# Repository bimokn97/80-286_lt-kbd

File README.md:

# 286_lt Mechanical Keyboard
A mechanical keyboard from old laptop called Goldstar GPC-4013B, with STM32F401 blackpill board, and additional serial output SN74HC595.

# choose firmware
  * Diy arduino firmware
      [download](https://github.com/bimokn97/80-286_lt-kbd/blob/master/stmduino_kbd/stmduino_kbd.ino) the .ino file, and open it using arduino software, than flash it.

  * [QMK Firmware](https://github.com/qmk/qmk_firmware.git) 
    * clone the repository     : `git clone https://github.com/bimokn97/qmk_firmware.git`
    * cd to directory          : `cd qmk_firmware`
    * switch to develop branch : `git checkout develop`
    * build it                 : `make 286_lt:default` or `make 286_lt:via` for costumable layout by [via](https://caniusevia.com)
   
   * [Vial Firmware](https://github.com/vial_qmk/vial.git)
     * clone the repository     : `git clone https://github.com/bimokn97/vial_qmk.git`
     * cd to directory          : `cd qmk_firmware`
     * switch to develop branch : `git checkout develop`
     * build it                 : `make 286_lt:vial` for costumable layout by [vial]([https://caniusevia.com](https://get.vial.today/))

# pcb layout and schematic
  using [Kicad](https://www.kicad.org/)
  * [keyboard pcb](https://github.com/bimokn97/80-286_lt-kbd/tree/master/schematic_pcb/keyboard)
  * [mcu connector board](https://github.com/bimokn97/80-286_lt-kbd/tree/master/schematic_pcb/mcu_board)
  
    connector FPC 22 pin 1mm pitch
  
  *

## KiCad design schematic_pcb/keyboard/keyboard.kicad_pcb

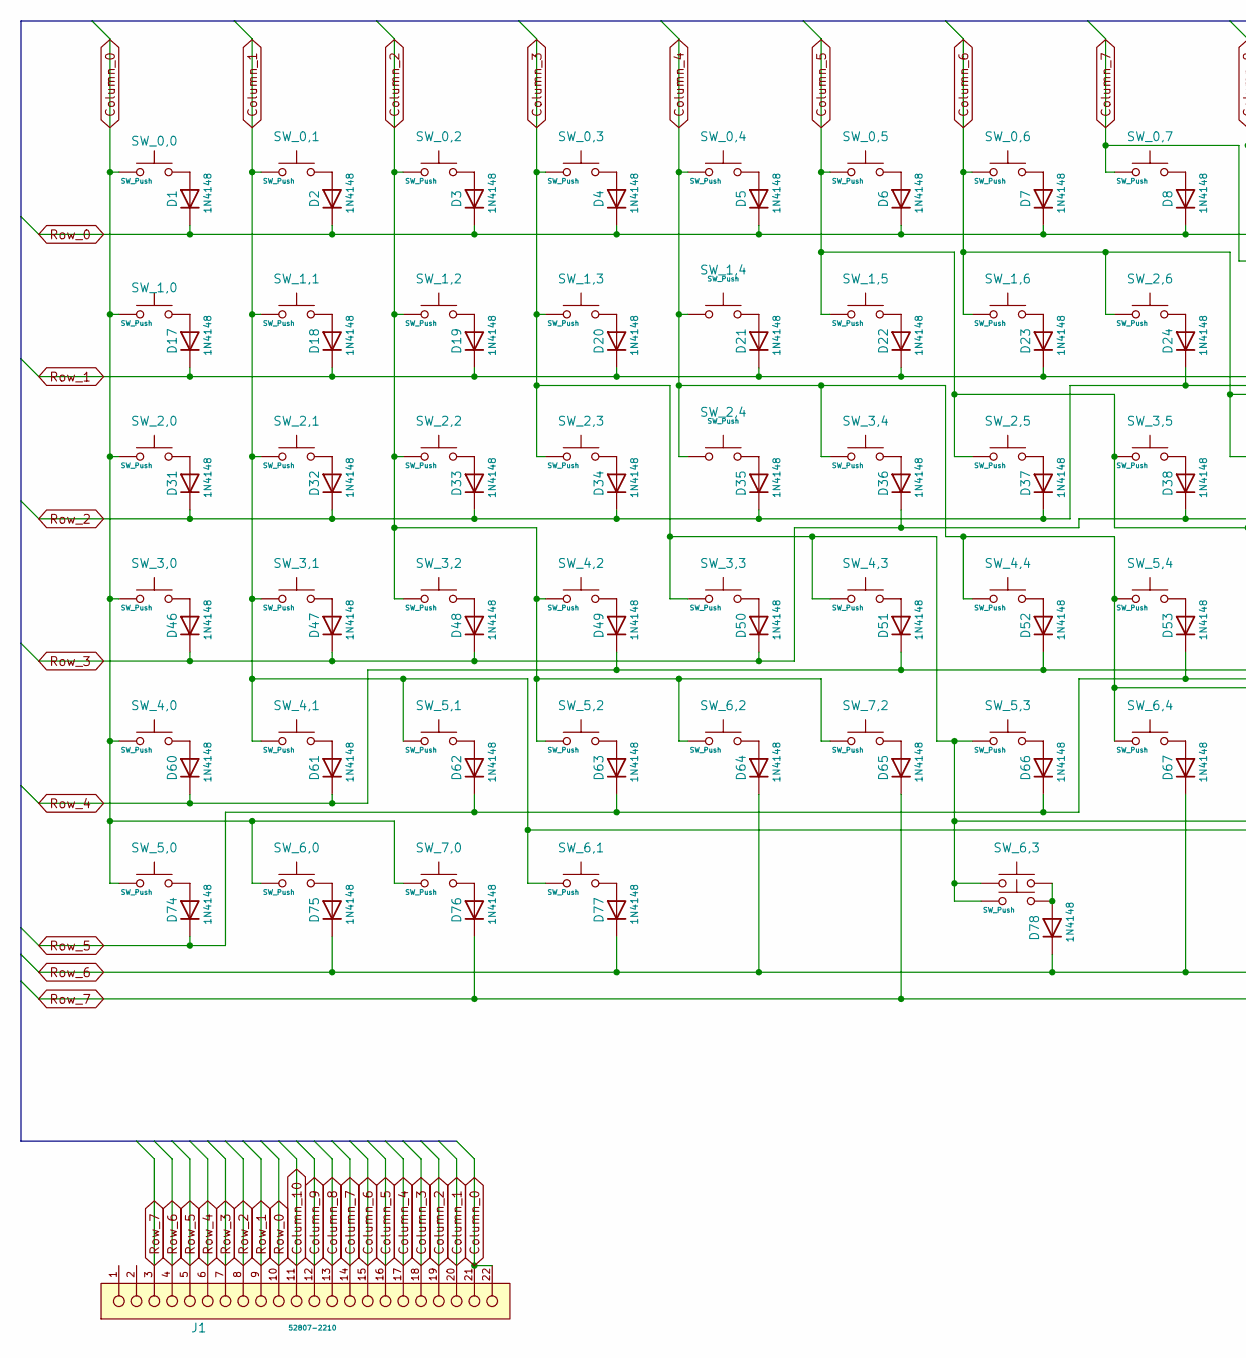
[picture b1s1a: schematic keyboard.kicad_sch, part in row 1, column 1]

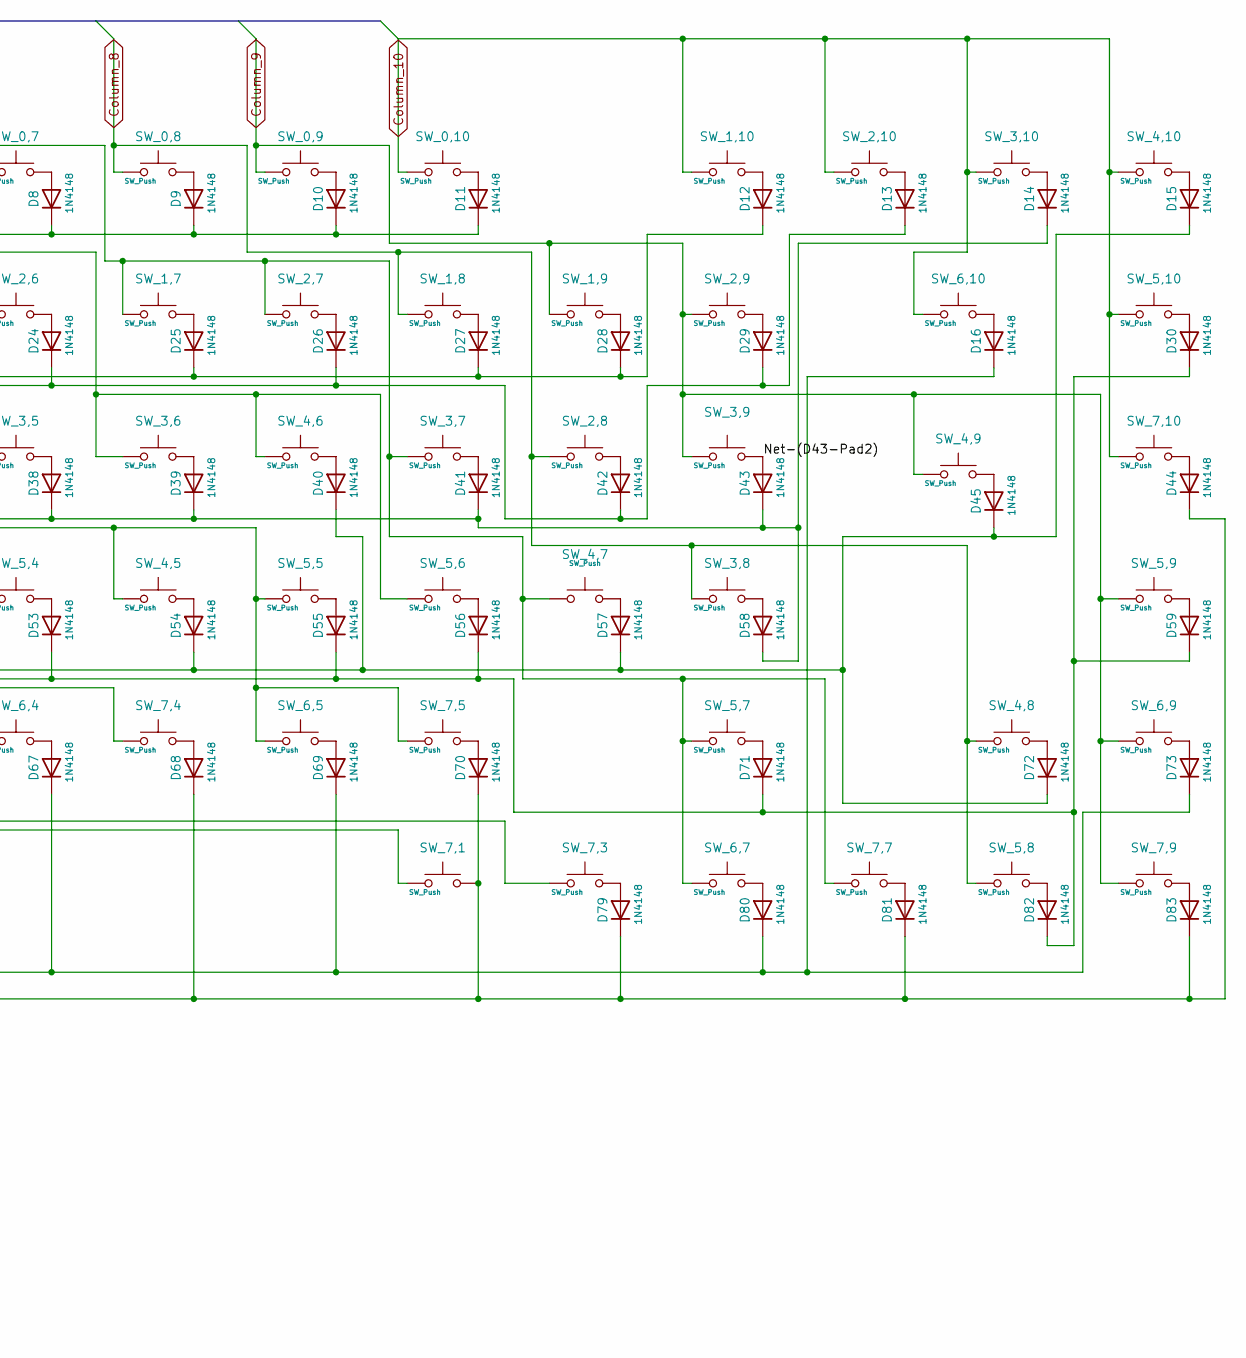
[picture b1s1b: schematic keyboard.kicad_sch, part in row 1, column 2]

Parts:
D1, D2, D3, D4, D5, D6, D7, D8, D9, D10, D11, D12, D13, D14, D15, D16, D17, D18, D19, D20, D21, D22, D23, D24, D25, D26, D27, D28, D29, D30, D31, D32, D36, D37, D38, D39, D40, D41, D42, D45, D46, D47, D48, D49, D50, D54, D55, D56, D57, D60, D61, D62, D63, D64, D65, D66, D67, D68, D69, D70, D71, D72, D76, D77, D79, D80, D81, D82: 1N4148; D_DO-35_SOD27_P12.70mm_Horizontal
D33, D34, D35, D43, D44, D51, D52, D53, D58, D59, D73, D74, D75, D83: 1N4148; D_DO-35_SOD27_P10.16mm_Horizontal
D78: 1N4148; D_DO-35_SOD27_P7.62mm_Horizontal
J1: 52807-2210; Molex-52807-2210-Manufacturer_Recommended; Voltage Max 50V
SW_0,0, SW_0,1, SW_0,2, SW_0,3, SW_0,4, SW_0,5, SW_0,6, SW_0,7, SW_0,8, SW_0,9, SW_0,10, SW_1,0, SW_1,1, SW_1,2, SW_1,3, SW_1,4, SW_1,5, SW_1,6, SW_1,7, SW_1,8, SW_1,9, SW_1,10, SW_2,1, SW_2,2, SW_2,3, SW_2,4, SW_2,5, SW_2,6, SW_2,7, SW_2,8, SW_2,9, SW_2,10, SW_3,1, SW_3,2, SW_3,3, SW_3,4, SW_3,5, SW_3,6, SW_3,7, SW_3,8, SW_3,9, SW_3,10, SW_4,1, SW_4,2, SW_4,3, SW_4,4, SW_4,5, SW_4,6, SW_4,7, SW_4,8, SW_4,10, SW_5,1, SW_5,2, SW_5,3, SW_5,4, SW_5,5, SW_5,6, SW_5,8, SW_5,9, SW_5,10, SW_6,1, SW_6,2, SW_6,4, SW_6,5, SW_6,7, SW_6,9, SW_7,0, SW_7,2, SW_7,3, SW_7,4, SW_7,5, SW_7,7, SW_7,9, SW_7,10: SW_Push; SW_Cherry_MX_Plate_1.00u
SW_2,0: SW_Push; SW_Cherry_MX_Plate_1.50u
SW_3,0, SW_5,7: SW_Push; SW_Cherry_MX_Plate_1.75u
SW_4,0: SW_Push; SW_Cherry_MX_Plate_2.25u
SW_4,9: SW_Push; SW_Cherry_MX_Plate_ISOEnter
SW_5,0, SW_6,0: SW_Push; SW_Cherry_MX_Plate_1.25u
SW_6,3, SW_6,3_1: SW_Push; SW_Cherry_MX_Plate_6.50u
SW_6,10: SW_Push; SW_Cherry_MX_Plate_2.00u
SW_7,1: SW_Push; SW_Cherry_MX_Plate

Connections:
/Net-(D43-Pad2): D43.2 (A), SW_3,9.1
Column_0: J1.21, J1.22, SW_0,0.2, SW_1,0.1, SW_2,0.1, SW_3,0.1, SW_4,0.1, SW_5,0.1, SW_6,0.1, SW_7,0.1
Column_1: J1.20, SW_0,1.1, SW_1,1.1, SW_2,1.1, SW_3,1.1, SW_4,1.1, SW_5,1.1, SW_6,1.1, SW_7,1.1
Column_2: J1.19, SW_0,2.2, SW_1,2.1, SW_2,2.1, SW_3,2.1, SW_4,2.1, SW_5,2.1, SW_6,2.1, SW_7,2.1
Column_3: J1.18, SW_0,3.2, SW_1,3.1, SW_2,3.1, SW_3,3.1, SW_4,3.1, SW_5,3.1, SW_6,3.2, SW_6,3_1.1, SW_7,3.1
Column_4: J1.17, SW_0,4.2, SW_1,4.2, SW_2,4.2, SW_3,4.1, SW_4,4.1, SW_5,4.1, SW_6,4.1, SW_7,4.1
Column_5: J1.16, SW_0,5.2, SW_1,5.1, SW_2,5.1, SW_3,5.1, SW_4,5.1, SW_5,5.1, SW_6,5.1, SW_7,5.1
Column_6: J1.15, SW_0,6.2, SW_1,6.1, SW_2,6.1, SW_3,6.2, SW_4,6.1, SW_5,6.1
Column_7: J1.14, SW_0,7.2, SW_1,7.1, SW_2,7.1, SW_3,7.1, SW_4,7.2, SW_5,7.1, SW_6,7.1, SW_7,7.1
Column_8: J1.13, SW_0,8.2, SW_1,8.1, SW_2,8.1, SW_3,8.1, SW_4,8.1, SW_5,8.1
Column_9: J1.12, SW_0,9.2, SW_1,9.1, SW_2,9.1, SW_3,9.2, SW_4,9.1, SW_5,9.2, SW_6,9.2, SW_7,9.2
Column_10: J1.11, SW_0,10.2, SW_1,10.2, SW_2,10.2, SW_3,10.2, SW_4,10.2, SW_5,10.1, SW_6,10.1, SW_7,10.1
unnamed: D1.2 (A), SW_0,0.1
unnamed: D2.2 (A), SW_0,1.2
unnamed: D3.2 (A), SW_0,2.1
unnamed: D4.2 (A), SW_0,3.1
unnamed: D5.2 (A), SW_0,4.1
unnamed: D6.2 (A), SW_0,5.1
unnamed: D7.2 (A), SW_0,6.1
unnamed: D8.2 (A), SW_0,7.1
unnamed: D9.2 (A), SW_0,8.1
unnamed: D10.2 (A), SW_0,9.1
unnamed: D11.2 (A), SW_0,10.1
unnamed: D12.2 (A), SW_1,10.1
unnamed: D13.2 (A), SW_2,10.1
unnamed: D14.2 (A), SW_3,10.1
unnamed: D15.2 (A), SW_4,10.1
unnamed: D16.2 (A), SW_6,10.2
unnamed: D17.2 (A), SW_1,0.2
unnamed: D18.2 (A), SW_1,1.2
unnamed: D19.2 (A), SW_1,2.2
unnamed: D20.2 (A), SW_1,3.2
unnamed: D21.2 (A), SW_1,4.1
unnamed: D22.2 (A), SW_1,5.2
unnamed: D23.2 (A), SW_1,6.2
unnamed: D24.2 (A), SW_2,6.2
unnamed: D25.2 (A), SW_1,7.2
unnamed: D26.2 (A), SW_2,7.2
unnamed: D27.2 (A), SW_1,8.2
unnamed: D28.2 (A), SW_1,9.2
unnamed: D29.2 (A), SW_2,9.2
unnamed: D30.2 (A), SW_5,10.2
unnamed: D31.2 (A), SW_2,0.2
unnamed: D32.2 (A), SW_2,1.2
unnamed: D33.2 (A), SW_2,2.2
unnamed: D34.2 (A), SW_2,3.2
unnamed: D35.2 (A), SW_2,4.1
unnamed: D36.2 (A), SW_3,4.2
unnamed: D37.2 (A), SW_2,5.2
unnamed: D38.2 (A), SW_3,5.2
unnamed: D39.2 (A), SW_3,6.1
unnamed: D40.2 (A), SW_4,6.2
unnamed: D41.2 (A), SW_3,7.2
unnamed: D42.2 (A), SW_2,8.2
unnamed: D44.2 (A), SW_7,10.2
unnamed: D45.2 (A), SW_4,9.2
unnamed: D46.2 (A), SW_3,0.2
unnamed: D47.2 (A), SW_3,1.2
unnamed: D48.2 (A), SW_3,2.2
unnamed: D49.2 (A), SW_4,2.2
unnamed: D50.2 (A), SW_3,3.2
unnamed: D51.2 (A), SW_4,3.2
unnamed: D52.2 (A), SW_4,4.2
unnamed: D53.2 (A), SW_5,4.2
unnamed: D54.2 (A), SW_4,5.2
unnamed: D55.2 (A), SW_5,5.2
unnamed: D56.2 (A), SW_5,6.2
unnamed: D57.2 (A), SW_4,7.1
unnamed: D58.2 (A), SW_3,8.2
unnamed: D59.2 (A), SW_5,9.1
unnamed: D60.2 (A), SW_4,0.2
unnamed: D61.2 (A), SW_4,1.2
unnamed: D62.2 (A), SW_5,1.2
unnamed: D63.2 (A), SW_5,2.2
unnamed: D64.2 (A), SW_6,2.2
unnamed: D65.2 (A), SW_7,2.2
unnamed: D66.2 (A), SW_5,3.2
unnamed: D67.2 (A), SW_6,4.2
unnamed: D68.2 (A), SW_7,4.2
unnamed: D69.2 (A), SW_6,5.2
unnamed: D70.2 (A), SW_7,5.2
unnamed: D71.2 (A), SW_5,7.2
unnamed: D72.2 (A), SW_4,8.2
unnamed: D73.2 (A), SW_6,9.1
unnamed: D74.2 (A), SW_5,0.2
unnamed: D75.2 (A), SW_6,0.2
unnamed: D76.2 (A), SW_7,0.2
unnamed: D77.2 (A), SW_6,1.2
unnamed: D78.2 (A), SW_6,3.1, SW_6,3_1.2
unnamed: D79.2 (A), SW_7,3.2
unnamed: D80.2 (A), SW_6,7.2
unnamed: D81.2 (A), SW_7,7.2
unnamed: D82.2 (A), SW_5,8.2
unnamed: D83.2 (A), SW_7,9.1
Row_0: D1.1 (K), D2.1 (K), D3.1 (K), D4.1 (K), D5.1 (K), D6.1 (K), D7.1 (K), D8.1 (K), D9.1 (K), D10.1 (K), D11.1 (K), J1.10
Row_1: D12.1 (K), D17.1 (K), D18.1 (K), D19.1 (K), D20.1 (K), D21.1 (K), D22.1 (K), D23.1 (K), D25.1 (K), D27.1 (K), D28.1 (K), J1.9
Row_2: D13.1 (K), D24.1 (K), D26.1 (K), D29.1 (K), D31.1 (K), D32.1 (K), D33.1 (K), D34.1 (K), D35.1 (K), D37.1 (K), D42.1 (K), J1.8
Row_3: D14.1 (K), D36.1 (K), D38.1 (K), D39.1 (K), D41.1 (K), D43.1 (K), D46.1 (K), D47.1 (K), D48.1 (K), D50.1 (K), D58.1 (K), J1.7
Row_4: D15.1 (K), D40.1 (K), D45.1 (K), D49.1 (K), D51.1 (K), D52.1 (K), D54.1 (K), D57.1 (K), D60.1 (K), D61.1 (K), D72.1 (K), J1.6
Row_5: D30.1 (K), D53.1 (K), D55.1 (K), D56.1 (K), D59.1 (K), D62.1 (K), D63.1 (K), D66.1 (K), D71.1 (K), D74.1 (K), D82.1 (K), J1.5
Row_6: D16.1 (K), D64.1 (K), D67.1 (K), D69.1 (K), D73.1 (K), D75.1 (K), D77.1 (K), D78.1 (K), D80.1 (K), J1.4
Row_7: D44.1 (K), D65.1 (K), D68.1 (K), D70.1 (K), D76.1 (K), D79.1 (K), D81.1 (K), D83.1 (K), J1.3, SW_7,1.2

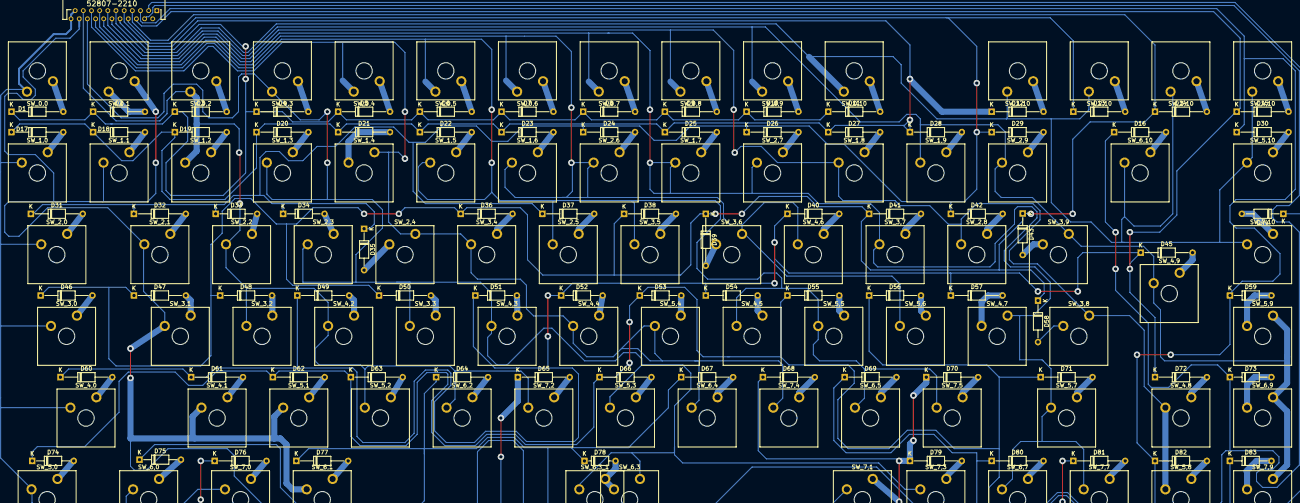
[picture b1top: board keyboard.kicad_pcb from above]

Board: 2 copper layers, 169 parts (0 on the bottom side), 102 nets.

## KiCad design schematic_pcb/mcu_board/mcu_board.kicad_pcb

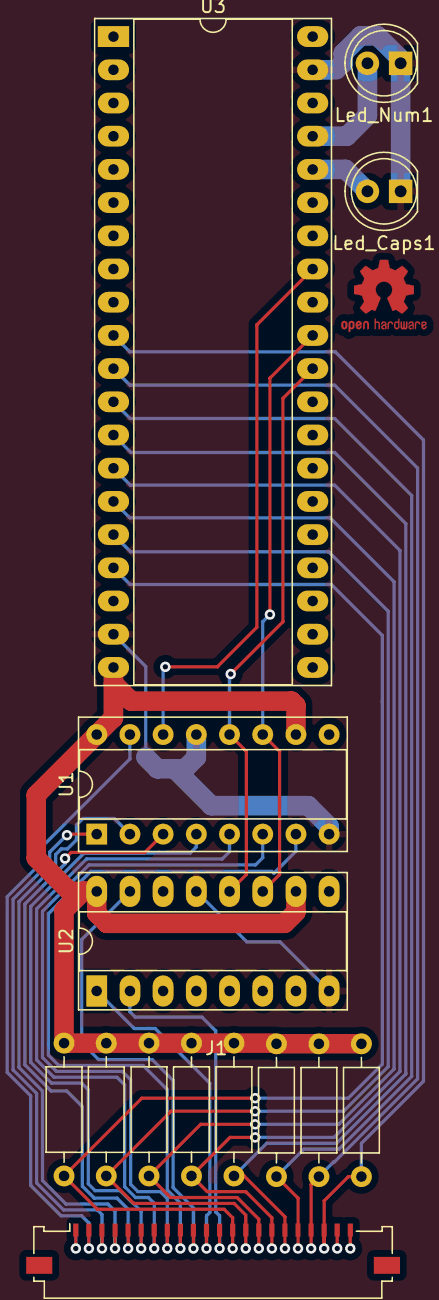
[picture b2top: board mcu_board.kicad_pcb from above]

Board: 2 copper layers, 14 parts (0 on the bottom side), 27 nets.

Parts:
J1: Conn_01x22; Molex_200528-0220_1x22-1MP_P1.00mm_Horizontal
Led_Caps1: LED; LED_D5.0mm
Led_Num1: LED; LED_D5.0mm
R1, R2, R3, R4, R5, R6, R7, R8: R 10 kΩ; R_Axial_DIN0207_L6.3mm_D2.5mm_P10.16mm_Horizontal
U1: 74HC595; DIP-16_W7.62mm_Socket
U2: 74HC595; DIP-16_W7.62mm_Socket_LongPads
U3: YAAJ_BlackPill_Part_Like; DIP-40_W15.24mm_Socket_LongPads

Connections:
+3V3: R1.2, R2.2, R3.2, R4.2, R5.2, R6.2, R7.2, R8.2, U1.10 (~SRCLR), U1.16 (VCC), U2.10 (~SRCLR), U2.16 (VCC), U3.20 (3V3)
Column_0: J1.2, U1.15 (QA)
Column_1: J1.3, U1.1 (QB)
Column_2: J1.4, U1.2 (QC)
Column_3: J1.5, U1.3 (QD)
Column_4: J1.6, U1.4 (QE)
Column_5: J1.7, U1.5 (QF)
Column_6: J1.8, U1.6 (QG)
Column_7: J1.9, U1.7 (QH)
Column_8: J1.10, U2.15 (QA)
Column_9: J1.11, U2.1 (QB)
Column_10: J1.12, U2.2 (QC)
GND: Led_Caps1.1 (K), Led_Num1.1 (K), U1.8 (GND), U1.13 (~OE), U2.8 (GND), U2.13 (~OE), U3.19 (GND), U3.39 (GND)
unnamed: Led_Caps1.2 (A), U3.36 (PB2)
unnamed: Led_Num1.2 (A), U3.37 (PB10)
unnamed: U1.9 (QH'), U2.14 (SER)
Row_0: J1.13, R1.1, U3.17 (PB9)
Row_1: J1.14, R2.1, U3.16 (PB8)
Row_2: J1.15, R3.1, U3.15 (PB7)
Row_3: J1.16, R4.1, U3.14 (PB6)
Row_4: J1.17, R5.1, U3.13 (PB5)
Row_5: J1.18, R6.1, U3.12 (PB4)
Row_6: J1.19, R7.1, U3.11 (PB3)
Row_7: J1.20, R8.1, U3.10 (PA15)
SPI_74HC595_SS: U1.12 (RCLK), U2.12 (RCLK), U3.30 (PA4)
SPI_MOSI: U1.14 (SER), U3.33 (PA7)
SPI_SCLK/CLK: U1.11 (SRCLK), U2.11 (SRCLK), U3.31 (PA5)

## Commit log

2022-06-26 add pcb layout
